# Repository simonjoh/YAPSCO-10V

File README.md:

# YAPSCO-10V
Modification of the YAPSC:10V with onboard -12V supply.

The board has the same outer dimensions and mounting hole positions as YAPSC:10V, so a drop-in replacement should be quite easy.

## Specifications
* Input voltage +12V..+24V
* Same as YAPSC:10V

## Schematic and PCB
Most of the schematic symbols have been updated with new ones from Kicad's library.

Some PCB footprints have been replaced with surface mounted versions to be able to squash in the -12V supply while keeping the board outline and mounting holes the same as YAPSC:10V.

The DB15 connector footprint has also been added to the PCB layout so that it can easily be soldered onto the board if needed.

The PCB now includes a DC-DC voltage inverter set to -12V, but can be adjusted as necessary with 2 feedback resistors (R28, R29). Component values for the DC-DC converter can be calculated with the SMath sheet "Calc MC33063.sm".

## Everything else
The firmware has not been modified and connectors are generally kept in the original places.

## Disclaimer
The board is being manufactured and therefore have not been tested yet. The only thing I have tested, is the DC-DC controller on a breadboard, but since everything has mainly been kept as the original it should just work right out of the box, right? :)

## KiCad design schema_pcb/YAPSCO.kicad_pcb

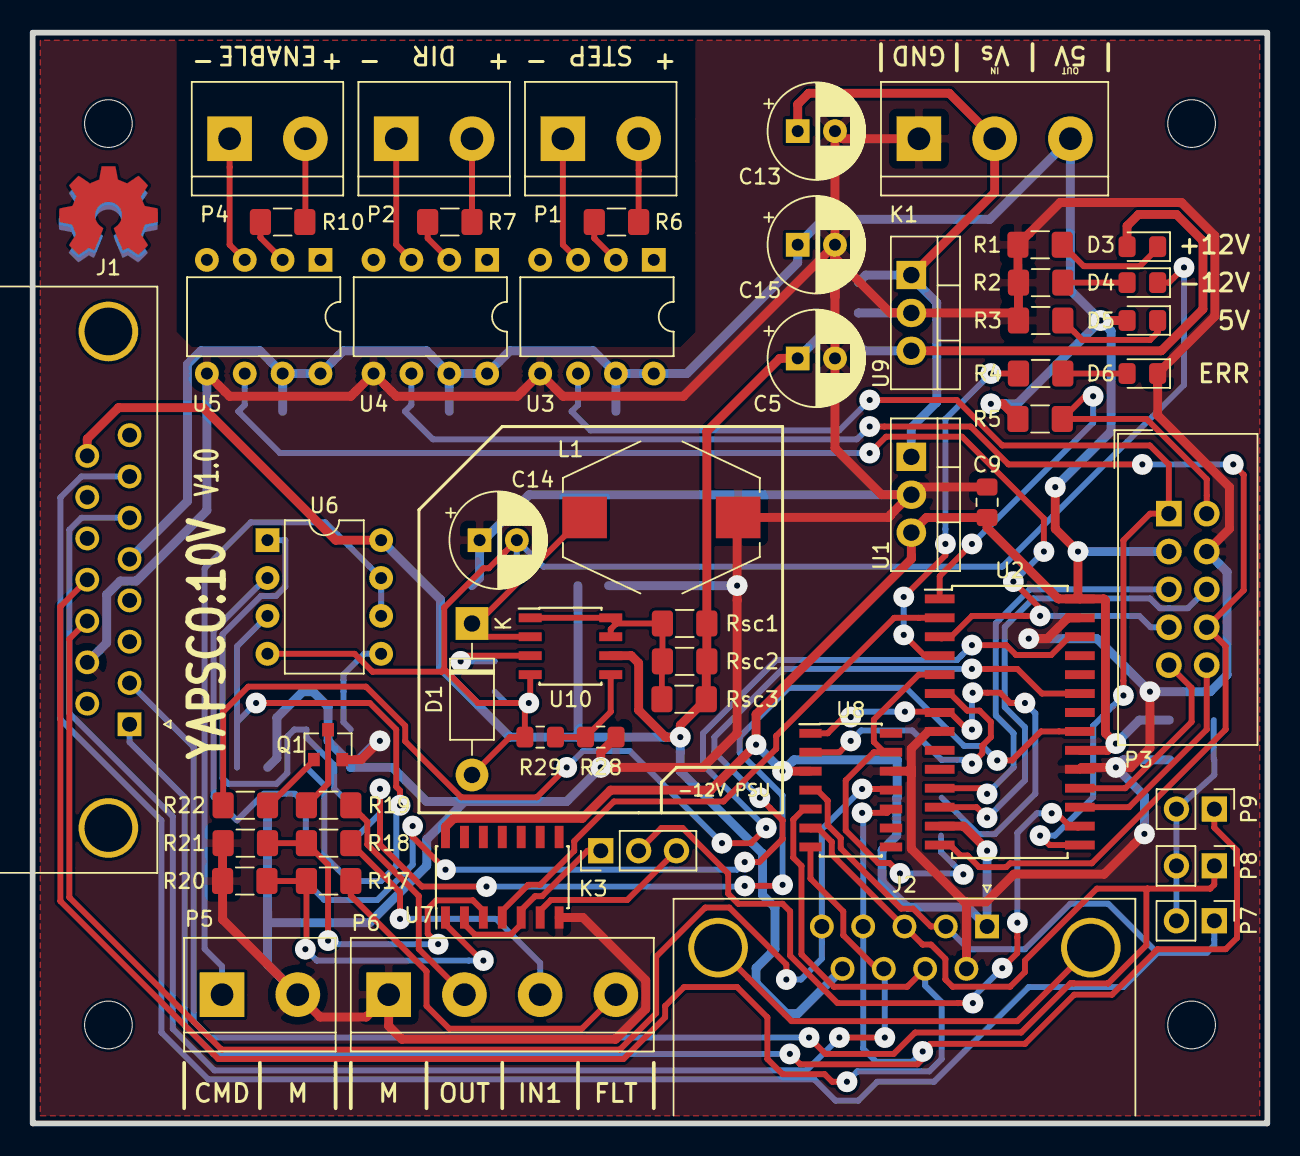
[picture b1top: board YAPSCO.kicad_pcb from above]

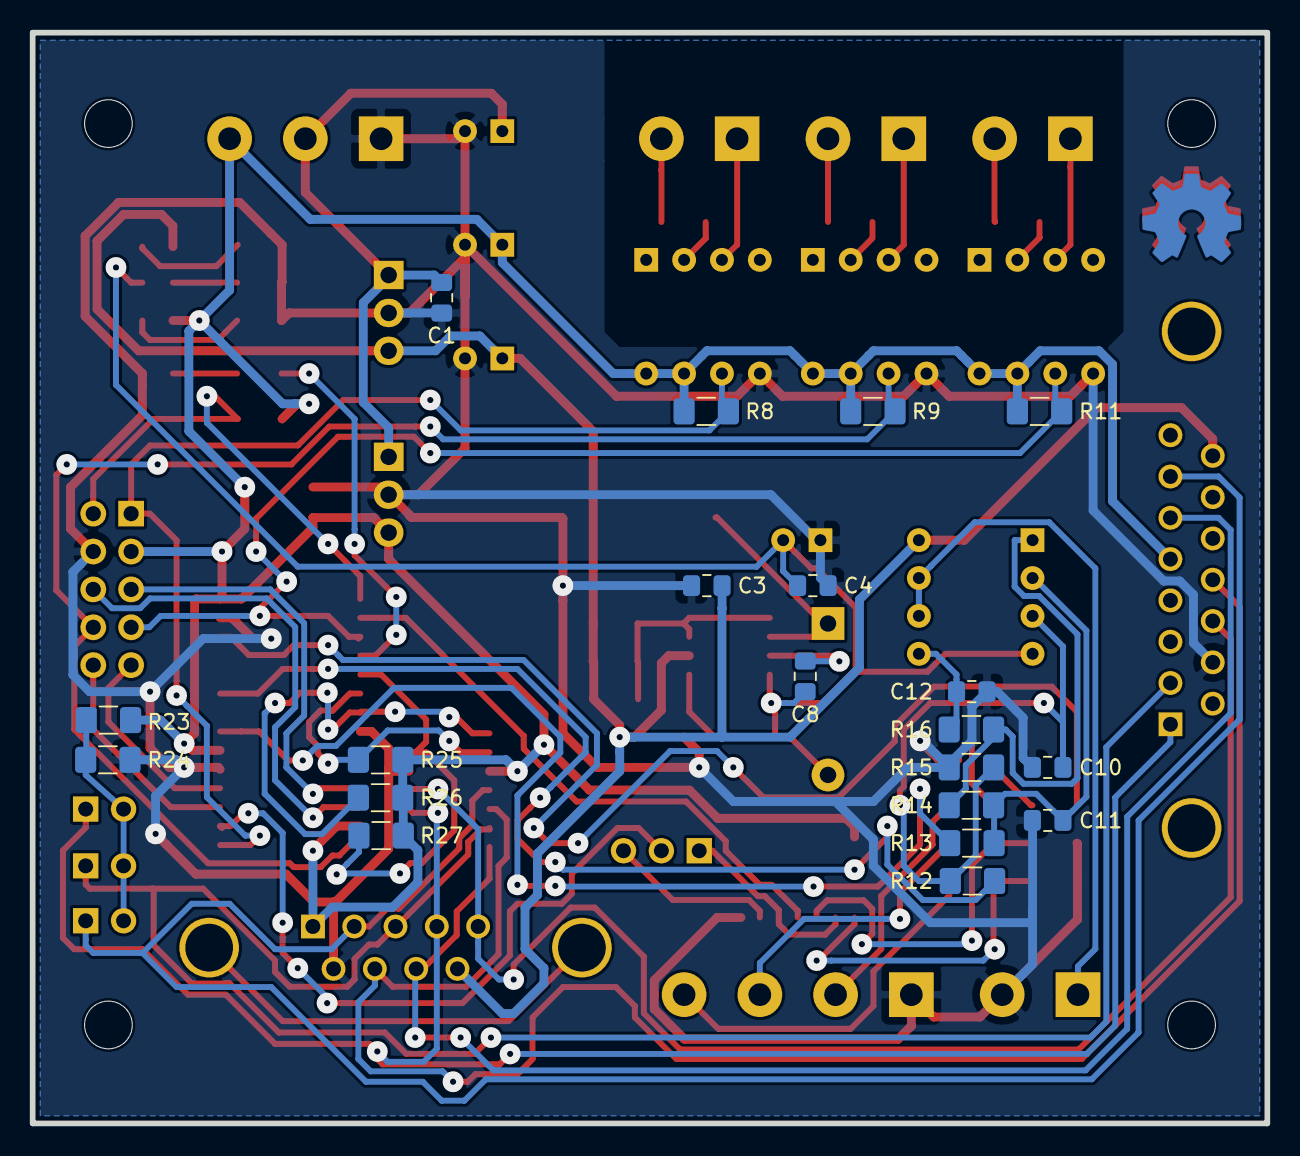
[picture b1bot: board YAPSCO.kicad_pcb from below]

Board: 2 copper layers, 82.8 x 73.2 mm, 78 parts (20 on the bottom side), 60 nets.

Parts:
C1, C3, C4, C9: 100nF; C_0805_2012Metric_Pad1.15x1.40mm_HandSolder
C5, C13, C15: 100uF; CP_Radial_D6.3mm_P2.50mm
C8: 360p; C_0805_2012Metric_Pad1.15x1.40mm_HandSolder
C10, C11, C12: 33nF; C_0805_2012Metric_Pad1.15x1.40mm_HandSolder
C14: 100u; CP_Radial_D6.3mm_P2.50mm
D1: 1N5819; D_DO-41_SOD81_P10.16mm_Horizontal
D3: +12; D_0805_2012Metric_Pad1.15x1.40mm_HandSolder
D4: -12; D_0805_2012Metric_Pad1.15x1.40mm_HandSolder
D5: LED 5V; LED_0805_2012Metric_Pad1.15x1.40mm_HandSolder
D6: LED; LED_0805_2012Metric_Pad1.15x1.40mm_HandSolder
H1, H2, H3, H4: MountingHole; MountingHole_3.2mm_M3_ISO7380
J1: DB15_Female; DSUB-15_Female_Horizontal_P2.77x2.84mm_EdgePinOffset9.90mm_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
J2: DB9_Female_MountingHoles; DSUB-9_Female_Horizontal_P2.77x2.84mm_EdgePinOffset9.90mm_H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
K1: Supply; TerminalBlock_bornier-3_P5.08mm
K3: FautlPol; PinHeader_1x03_P2.54mm_Vertical
L1: 1m; L_Bourns-SRR1005
P1: STEP; TerminalBlock_bornier-2_P5.08mm
P2: DIR; TerminalBlock_bornier-2_P5.08mm
P3: CONN; IDC-Header_2x05_P2.54mm_Vertical
P4: ENABLE; TerminalBlock_bornier-2_P5.08mm
P5: +-10V; TerminalBlock_bornier-2_P5.08mm
P6: InOut; TerminalBlock_bornier-4_P5.08mm
P7, P8, P9: Jumper; PinHeader_1x02_P2.54mm_Vertical
Q1: NPN; SOT-23
R1, R2: 2K2; R_1206_3216Metric_Pad1.42x1.75mm_HandSolder
R3, R4, R6, R7, R10: 470; R_1206_3216Metric_Pad1.42x1.75mm_HandSolder
R5: 10K; R_1206_3216Metric_Pad1.42x1.75mm_HandSolder
R8, R9, R11, R25, R26, R27: 4K7; R_1206_3216Metric_Pad1.42x1.75mm_HandSolder
R12, R13: 22K; R_1206_3216Metric_Pad1.42x1.75mm_HandSolder
R14, R15: 47K; R_1206_3216Metric_Pad1.42x1.75mm_HandSolder
R16: 22k; R_1206_3216Metric_Pad1.42x1.75mm_HandSolder
R17, R18, R20, R21: R; R_1206_3216Metric_Pad1.42x1.75mm_HandSolder
R19: 100; R_1206_3216Metric_Pad1.42x1.75mm_HandSolder
R22, R23, R24: 1K; R_1206_3216Metric_Pad1.42x1.75mm_HandSolder
R28: 8K6; R_0805_2012Metric_Pad1.15x1.40mm_HandSolder
R29: 1K; R_0805_2012Metric_Pad1.15x1.40mm_HandSolder
Rsc1, Rsc2, Rsc3: 1R; R_1206_3216Metric_Pad1.42x1.75mm_HandSolder
U1: 7805; TO-220-3_Vertical
U2: dsPIC30F4012; SOIC-28W_7.5x17.9mm_P1.27mm
U3, U4, U5: 6N137; DIP-8_W7.62mm
U6: LM358; DIP-8_W7.62mm
U7: 74HC14; SOIC-14_3.9x8.7mm_P1.27mm
U8: LM339D; SOIC-14_3.9x8.7mm_P1.27mm
U9: L7812; TO-220-3_Vertical
U10: MC33063AD; SOIC-8_3.9x4.9mm_P1.27mm

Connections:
+2V5: P7.2, P8.2, P9.2, R23.2, R24.1
+5V: C9.1, C15.1, D5.2, J1.5, J2.1, K1.3, P3.3, R5.1, R8.1, R9.1, R11.1, R23.1, R25.1, R26.1, R27.1, U1.3, U2.13, U2.20, U2.28, U3.7, U3.8, U4.7, U4.8, U5.7, U5.8, U7.14, U8.3
+12V: C3.1, C5.1, D3.2, J1.15, J2.9, Rsc1.2, Rsc2.2, Rsc3.2, U6.8, U9.3, U10.6
-12V: C4.2, C8.2, C14.2, D1.2, D4.1, R29.2, U6.4, U10.4
/Encoder/A+: J1.12, J2.7, U8.5
/Encoder/A-: J1.7, J2.2, P7.1, U8.4
/Encoder/B+: J1.6, J2.8, U8.7
/Encoder/B-: J1.2, J2.3, P8.1, U8.6
/Encoder/I+: J1.11, J2.5, U8.11
/Encoder/I-: J1.1, J2.4, P9.1, U8.10
/Encoder/INDX: R27.2, U2.5, U8.13
/Encoder/QEA: R25.2, U2.6, U8.2
/Encoder/QEB: R26.2, U2.7, U8.1
/InterfaceDriver/FLTA: K3.2, U2.16
/InterfaceDriver/IN1: U2.2, U7.4
/InterfaceDriver/Neg: R13.2, U2.21
/InterfaceDriver/OUT1: R22.1, U2.26
/MotionControllerInput/DIR: P3.8, R9.2, U2.14, U4.6
/MotionControllerInput/ENABLE: P3.7, R11.2, U2.3, U5.6
/MotionControllerInput/MCLR: P3.2, R5.2, U2.1
/MotionControllerInput/PGC: P3.9, U2.18
/MotionControllerInput/PGD: P3.10, U2.17
/MotionControllerInput/STEP: P3.1, R8.2, U2.15, U3.6
/SupplyCircuit/InputVoltageRail: C1.1, C13.1, K1.2, U1.1, U9.1
/dsPIC/PWM_H_A: R12.2, U2.23
/dsPIC/RX: P3.6, U2.12
/dsPIC/TX: P3.5, U2.11
GND: C1.2, C3.2, C4.1, C5.2, C9.2, C10.1, C11.2, C12.2, C13.2, C14.1, C15.2, D6.1, J1.10, J2.6, K1.1, L1.2, P3.4, P5.2, P6.1, Q1.2, R1.1, R2.1, R3.2, R15.1, R20.1, R21.1, R24.2, R28.2, U1.2, U2.8, U2.19, U2.27, U3.5, U4.5, U5.5, U7.7, U8.12, U9.2
unnamed: C8.1, U10.3
unnamed: C10.2, R12.1, R15.2, U6.3
unnamed: C11.1, R13.1, R14.2, U6.2
unnamed: C12.1, R16.1, U6.5
unnamed: D1.1, L1.1, U10.2
unnamed: D3.1, R1.2
unnamed: D4.2, R2.2
unnamed: D5.1, R3.1
unnamed: D6.2, R4.2
unnamed: K3.1, U7.2, U7.5
unnamed: K3.3, U7.6
unnamed: P1.1, U3.3
unnamed: P1.2, R6.2
unnamed: P2.1, U4.3
unnamed: P2.2, R7.2
unnamed: P4.1, U5.3
unnamed: P4.2, R10.2
unnamed: P5.1, U6.6, U6.7
unnamed: P6.2, R19.2
unnamed: P6.3, R18.2
unnamed: P6.4, R17.2
unnamed: Q1.1, R22.2
unnamed: Q1.3, R19.1
unnamed: R4.1, U2.4
unnamed: R6.1, U3.2
unnamed: R7.1, U4.2
unnamed: R10.1, U5.2
unnamed: R14.1, R16.2, U6.1
unnamed: R17.1, R20.2, U7.1
unnamed: R18.1, R21.2, U7.3
unnamed: R28.1, R29.1, U10.5
unnamed: Rsc1.1, Rsc2.1, Rsc3.1, U10.1, U10.7, U10.8

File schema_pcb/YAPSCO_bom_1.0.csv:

Component,Description,Part,References,Value,Footprint,Quantity Per PCB,Datasheet
1,Unpolarized capacitor,C,C1 C3 C4 C9,100nF,C_0805_2012Metric_Pad1.15x1.40mm_HandSolder,4,
2,Polarized capacitor,CP,C5 C13 C14 C15,100uF,CP_Radial_D6.3mm_P2.50mm,4,
3,Unpolarized capacitor,C,C10 C11 C12,33nF,C_0805_2012Metric_Pad1.15x1.40mm_HandSolder,3,
4,Unpolarized capacitor,C,C8,360p,C_0805_2012Metric_Pad1.15x1.40mm_HandSolder,1,
5,Light emitting diode,LED,D3,+12,D_0805_2012Metric_Pad1.15x1.40mm_HandSolder,1,
6,Light emitting diode,LED,D4,-12,D_0805_2012Metric_Pad1.15x1.40mm_HandSolder,1,
7,Schottky diode,D_Schottky,D1,1N5819,D_DO-41_SOD81_P10.16mm_Horizontal,1,~
8,Light emitting diode,LED,D6,LED,LED_0805_2012Metric_Pad1.15x1.40mm_HandSolder,1,
9,Light emitting diode,LED,D5,LED 5V,LED_0805_2012Metric_Pad1.15x1.40mm_HandSolder,1,
10,"Generic connector, single row, 01x03, script generated (kicad-library-utils/schlib/autogen/connector/)",Conn_01x03_Male,K3,FautlPol,PinHeader_1x03_P2.54mm_Vertical,1,
11,"Generic screw terminal, single row, 01x03, script generated (kicad-library-utils/schlib/autogen/connector/)",Screw_Terminal_01x03,K1,Supply,TerminalBlock_bornier-3_P5.08mm,1,
12,Inductor,L,L1,1m,L_Bourns-SRR1005,1,~
13,"Generic screw terminal, single row, 01x02, script generated (kicad-library-utils/schlib/autogen/connector/)",Screw_Terminal_01x02,P5,+-10V,TerminalBlock_bornier-2_P5.08mm,1,
14,"Generic connector, double row, 02x05, odd/even pin numbering scheme (row 1 odd numbers, row 2 even numbers), script generated (kicad-library-utils/schlib/autogen/connector/)",Conn_02x05_Odd_Even,P3,CONN,IDC-Header_2x05_P2.54mm_Vertical,1,
15,"Generic screw terminal, single row, 01x02, script generated (kicad-library-utils/schlib/autogen/connector/)",Screw_Terminal_01x02,P2,DIR,TerminalBlock_bornier-2_P5.08mm,1,
16,"Generic screw terminal, single row, 01x02, script generated (kicad-library-utils/schlib/autogen/connector/)",Screw_Terminal_01x02,P4,ENABLE,TerminalBlock_bornier-2_P5.08mm,1,
17,"Generic screw terminal, single row, 01x04, script generated (kicad-library-utils/schlib/autogen/connector/)",Screw_Terminal_01x04,P6,InOut,TerminalBlock_bornier-4_P5.08mm,1,
18,"Jumper, 2-pole, open",Jumper_2_Open,P7 P8 P9,Jumper,PinHeader_1x02_P2.54mm_Vertical,3,
19,"Generic screw terminal, single row, 01x02, script generated (kicad-library-utils/schlib/autogen/connector/)",Screw_Terminal_01x02,P1,STEP,TerminalBlock_bornier-2_P5.08mm,1,
20,"NPN transistor, base/emitter/collector",Q_NPN_BEC,Q1,NPN,SOT-23,1,
21,Resistor,R,R19,100,R_1206_3216Metric_Pad1.42x1.75mm_HandSolder,1,
22,Resistor,R,R5,10K,R_1206_3216Metric_Pad1.42x1.75mm_HandSolder,1,
23,Resistor,R,R22 R23 R24,1K,R_1206_3216Metric_Pad1.42x1.75mm_HandSolder,3,
24,Resistor,R,R29,1K,R_0805_2012Metric_Pad1.15x1.40mm_HandSolder,1,~
25,Resistor,R,R12 R13 R16,22K,R_1206_3216Metric_Pad1.42x1.75mm_HandSolder,3,
26,Resistor,R,R1 R2,2K2,R_1206_3216Metric_Pad1.42x1.75mm_HandSolder,2,
27,Resistor,R,R3 R4 R6 R7 R10,470,R_1206_3216Metric_Pad1.42x1.75mm_HandSolder,5,
28,Resistor,R,R14 R15,47K,R_1206_3216Metric_Pad1.42x1.75mm_HandSolder,2,
29,Resistor,R,R8 R9 R11 R25 R26 R27,4K7,R_1206_3216Metric_Pad1.42x1.75mm_HandSolder,6,
30,Resistor,R,R28,8K6,R_0805_2012Metric_Pad1.15x1.40mm_HandSolder,1,~
31,Resistor,R,R17 R18 R20 R21,R,R_1206_3216Metric_Pad1.42x1.75mm_HandSolder,4,
32,Resistor,R,Rsc1 Rsc2 Rsc3,1R,R_1206_3216Metric_Pad1.42x1.75mm_HandSolder,3,~
33,,6N137,U3 U4 U5,6N137,DIP-8_W7.62mm,3,
34,Hex inverter schmitt trigger,74HC14,U7,74HC14,SOIC-14_3.9x8.7mm_P1.27mm,1,http://www.nxp.com/documents/data_sheet/74HC_HCT04.pdf
35,"Positive 1A 35V Linear Regulator, Fixed Output 5V, TO-220",LM7805_TO220,U1,7805,TO-220-3_Vertical,1,http://www.fairchildsemi.com/ds/LM/LM7805.pdf
36,"Positive 1.5A 35V Linear Regulator, Fixed Output 12V, TO-220/TO-263/TO-252",L7812,U9,L7812,TO-220-3_Vertical,1,http://www.st.com/content/ccc/resource/technical/document/da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
37,"Quad Differential Comparators, DIP-14/SOIC-14/SSOP-14",LM339,U8,LM339D,SOIC-14_3.9x8.7mm_P1.27mm,1,http://www.ti.com/lit/ds/symlink/lm339.pdf
38,"Low-Power, Dual Operational Amplifiers, DIP-8/SOIC-8/TO-99-8",LM358,U6,LM358,DIP-8_W7.62mm,1,http://www.ti.com/lit/ds/symlink/lm358.pdf
39,"1.5A, step-up/down/inverting switching regulator, 3-40V Vin, 100kHz, SO-8",MC33063AD,U10,MC33063AD,SOIC-8_3.9x4.9mm_P1.27mm,1,http://www.onsemi.com/pub_link/Collateral/MC34063A-D.PDF
40,,DSPIC30F4012-20E_SO,U2,dsPIC30F4012,SOIC-28W_7.5x17.9mm_P1.27mm,1,Microchip





Component Groups:,40
Component Count:,72
Fitted Components:,72
Number of PCBs:,1
Total components:,72
Schematic Version:,1.0
Schematic Date:,2019-03-30
BoM Date:,05-04-2019 17:39:44
Schematic Source:,E:\OneDrive\Dokumenter\DIY\Projekter\HJF CNC\YAPSC.10V\schema_pcb\current\YAPSCO.sch
KiCad Version:,Eeschema (5.1.0)-1

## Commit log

2019-04-06 Project files added
2019-05-01 Removed cutout from manual in InterfaceDriver
2019-05-01 Added 3D STEP file of board
2019-05-02 Updated DigiKey BOM
2019-05-02 Added keep-out area around opto-isolators
